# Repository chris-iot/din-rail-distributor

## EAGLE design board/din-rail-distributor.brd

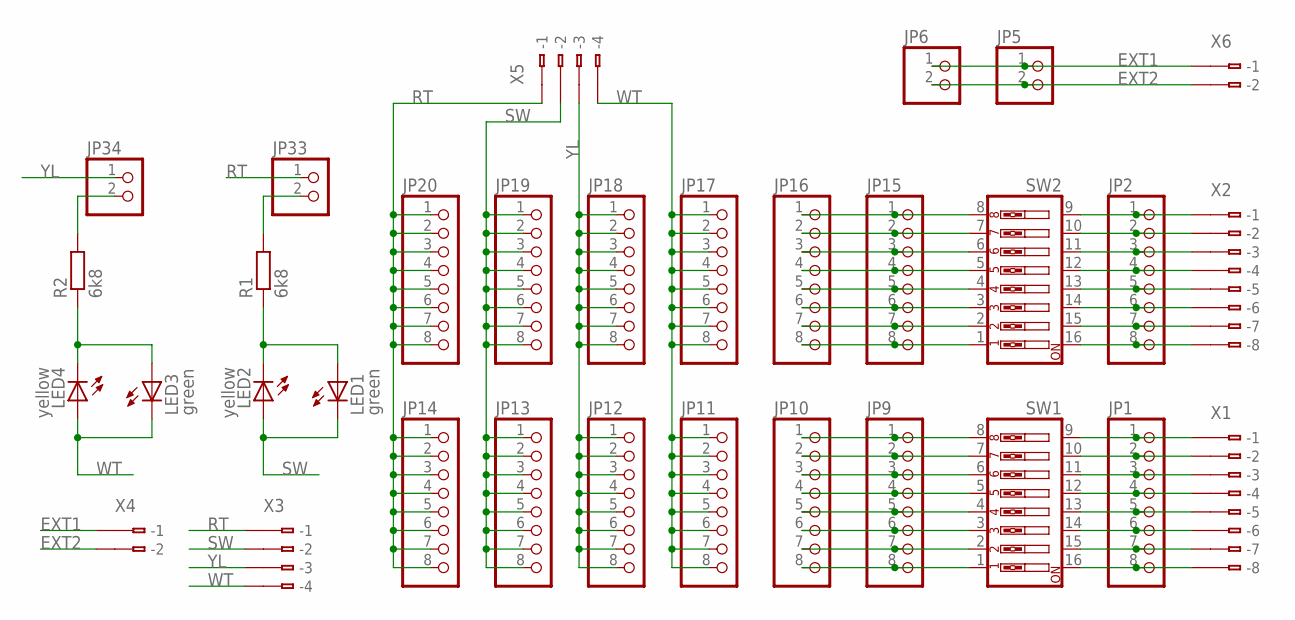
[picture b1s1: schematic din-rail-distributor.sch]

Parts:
JP1, JP2: PINHD-1X8; 1X08
JP5, JP6, JP33, JP34: PINHD-1X2; 1X02
JP9, JP10, JP11, JP12, JP13, JP14, JP15, JP16, JP17, JP18, JP19, JP20: PINHD-1X8/SMALL; 1X08/SMALL
LED1, LED3: green; CHIP-LED0603
LED2, LED4: yellow; CHIP-LED0603
R1, R2: 6k8; R1206
SW1, SW2: SW_DIP-8; EDG-08
X1, X2: 233-108
X3, X5: 233-104
X4, X6: 233-102

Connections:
EXT1: JP5.1, JP6.1, X4.B1 (B-1), X6.B1 (B-1)
EXT2: JP5.2, JP6.2, X4.B2 (B-2), X6.B2 (B-2)
unnamed: JP1.8, SW1.16, X1.B8 (B-8)
unnamed: JP1.7, SW1.15, X1.B7 (B-7)
unnamed: JP1.6, SW1.14, X1.B6 (B-6)
unnamed: JP1.5, SW1.13, X1.B5 (B-5)
unnamed: JP1.4, SW1.12, X1.B4 (B-4)
unnamed: JP1.3, SW1.11, X1.B3 (B-3)
unnamed: JP1.2, SW1.10, X1.B2 (B-2)
unnamed: JP1.1, SW1.9, X1.B1 (B-1)
unnamed: JP2.8, SW2.16, X2.B8 (B-8)
unnamed: JP2.7, SW2.15, X2.B7 (B-7)
unnamed: JP2.6, SW2.14, X2.B6 (B-6)
unnamed: JP2.5, SW2.13, X2.B5 (B-5)
unnamed: JP2.4, SW2.12, X2.B4 (B-4)
unnamed: JP2.3, SW2.11, X2.B3 (B-3)
unnamed: JP2.2, SW2.10, X2.B2 (B-2)
unnamed: JP2.1, SW2.9, X2.B1 (B-1)
unnamed: JP15.1, JP16.1, SW2.8
unnamed: JP15.2, JP16.2, SW2.7
unnamed: JP15.3, JP16.3, SW2.6
unnamed: JP15.4, JP16.4, SW2.5
unnamed: JP15.5, JP16.5, SW2.4
unnamed: JP15.6, JP16.6, SW2.3
unnamed: JP15.7, JP16.7, SW2.2
unnamed: JP15.8, JP16.8, SW2.1
unnamed: JP9.1, JP10.1, SW1.8
unnamed: JP9.2, JP10.2, SW1.7
unnamed: JP9.3, JP10.3, SW1.6
unnamed: JP9.4, JP10.4, SW1.5
unnamed: JP9.5, JP10.5, SW1.4
unnamed: JP9.6, JP10.6, SW1.3
unnamed: JP9.7, JP10.7, SW1.2
unnamed: JP9.8, JP10.8, SW1.1
unnamed: JP33.2, R1.2
unnamed: LED1.A, LED2.C, R1.1
unnamed: JP34.2, R2.2
unnamed: LED3.A, LED4.C, R2.1
RT: JP14.1, JP14.2, JP14.3, JP14.4, JP14.5, JP14.6, JP14.7, JP14.8, JP20.1, JP20.2, JP20.3, JP20.4, JP20.5, JP20.6, JP20.7, JP20.8, JP33.1, X3.B1 (B-1), X5.B1 (B-1)
SW: JP13.1, JP13.2, JP13.3, JP13.4, JP13.5, JP13.6, JP13.7, JP13.8, JP19.1, JP19.2, JP19.3, JP19.4, JP19.5, JP19.6, JP19.7, JP19.8, LED1.C, LED2.A, X3.B2 (B-2), X5.B2 (B-2)
WT: JP11.1, JP11.2, JP11.3, JP11.4, JP11.5, JP11.6, JP11.7, JP11.8, JP17.1, JP17.2, JP17.3, JP17.4, JP17.5, JP17.6, JP17.7, JP17.8, LED3.C, LED4.A, X3.B4 (B-4), X5.B4 (B-4)
YL: JP12.1, JP12.2, JP12.3, JP12.4, JP12.5, JP12.6, JP12.7, JP12.8, JP18.1, JP18.2, JP18.3, JP18.4, JP18.5, JP18.6, JP18.7, JP18.8, JP34.1, X3.B3 (B-3), X5.B3 (B-3)

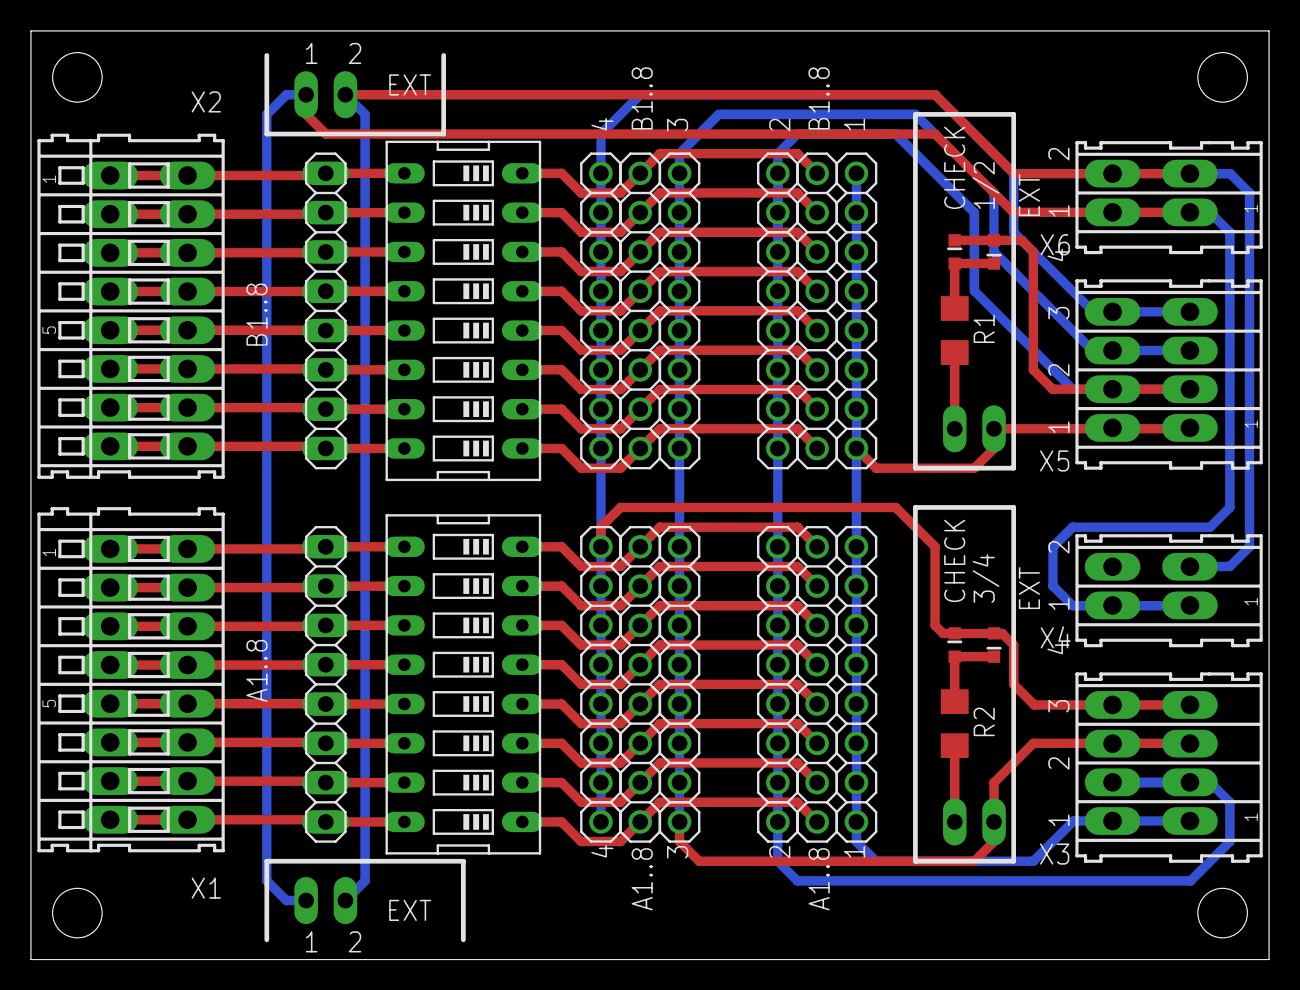
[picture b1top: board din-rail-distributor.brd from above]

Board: 2 copper layers, 80.0 x 60.0 mm, 32 parts (0 on the bottom side), 42 nets.

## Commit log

2020-04-05 First manufactured version
